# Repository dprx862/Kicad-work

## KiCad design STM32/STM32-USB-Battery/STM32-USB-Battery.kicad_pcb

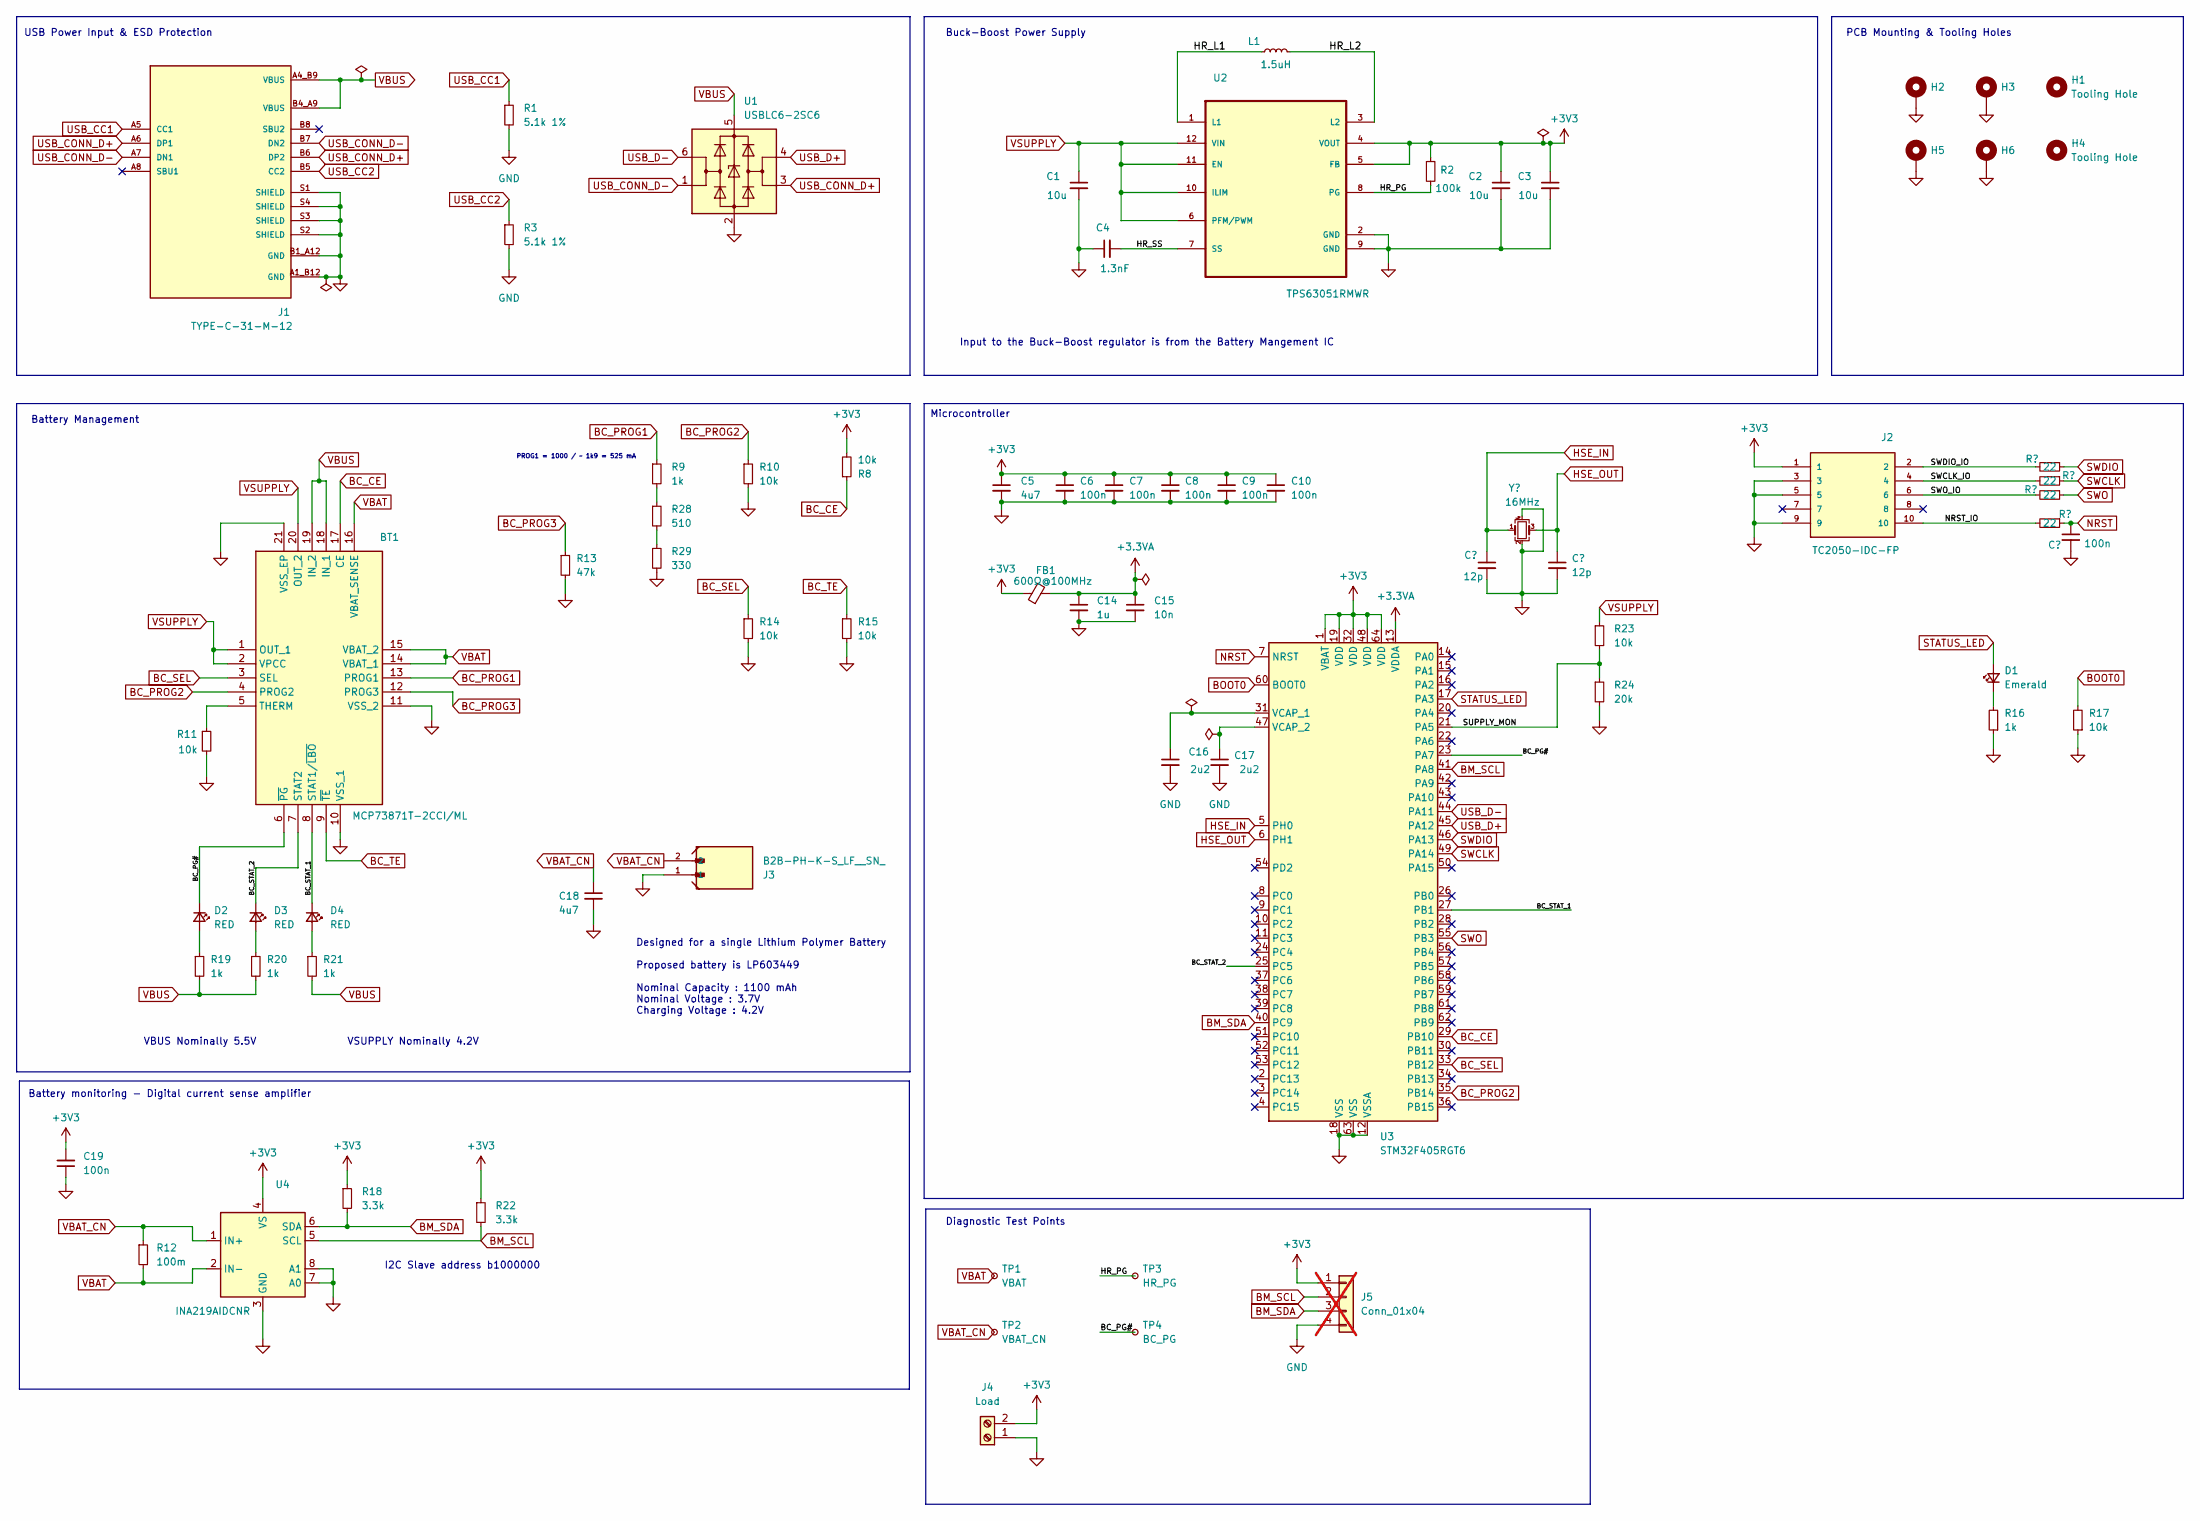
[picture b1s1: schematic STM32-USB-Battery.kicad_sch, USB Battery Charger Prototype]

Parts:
BT1: MCP73871T-2CCI/ML; QFN50P400X400X100-21M-D; Mouser Part Number 579-MCP73871T2CCIML
C1, C2, C3: 10u; C_0603_1608Metric; LCSC Part # C96446
C4: 1.3nF; C_0402_1005Metric; LCSC Part # C1523
C5, C18: 4u7; C_0603_1608Metric; LCSC Part # C19666
C6, C7, C8, C9, C10, C11, C19: 100n; C_0402_1005Metric; LCSC Part # C1525
C12, C13: 12p; C_0402_1005Metric; LCSC Part # C1547
C14: 1u; C_0402_1005Metric; LCSC Part # C52923
C15: 10n; C_0402_1005Metric; LCSC Part # C15195
C16, C17: 2u2; C_0603_1608Metric; LCSC Part # C23630
D1: Emerald; LED_0805_2012Metric; LCSC Part # C2297
D2, D3, D4: RED; LED_0603_1608Metric; LCSC Part # C2286
FB1: 600Ω@100MHz; L_0805_2012Metric; LCSC Part # C1017
H1, H4: Tooling Hole; JLC Tooling Hole
H2, H3, H5, H6: MountingHole_Pad; MountingHole_3.2mm_M3_DIN965_Pad_TopBottom
J1: TYPE-C-31-M-12; HRO_TYPE-C-31-M-12; PARTREV 2020.12.08; LCSC Part # C165948
J2: TC2050-IDC-FP; Tag-Connect_TC2050-IDC-FP_2x05_P1.27mm_Vertical
J3: B2B-PH-K-S_LF__SN_; JST_B2B-PH-K-S_LF__SN_
J4: Load; 1760510000
J5: Conn_01x04; PinHeader_1x04_P2.54mm_Vertical; not fitted
L1: 1.5uH; L_1008_2520Metric; LCSC Part # C98034
R1, R3: 5.1k 1%; R_0402_1005Metric; LCSC Part # C25905
R2: 100k; R_0402_1005Metric; LCSC Part # C25741
R4, R5, R6, R7: 22; R_0402_1005Metric; LCSC Part # C25092
R8, R10, R11, R14, R15, R17, R23: 10k; R_0402_1005Metric; LCSC Part # C25744
R9, R16, R19, R20, R21: 1k; R_0402_1005Metric; LCSC Part # C11702
R12: 100m; R_1206_3216Metric; LCSC Part # C2903496
R13: 47k; R_0402_1005Metric; LCSC Part # C25792
R18, R22: 3.3k; R_0402_1005Metric; LCSC Part # C25890
R24: 20k; R_0402_1005Metric; LCSC Part # C25765
R28: 510; R_0402_1005Metric; LCSC Part # C25123
R29: 330; R_0402_1005Metric; LCSC Part # C25104
TP1: VBAT; TestPoint_Pad_D1.0mm
TP2: VBAT_CN; TestPoint_Pad_D1.0mm
TP3: HR_PG; TestPoint_Pad_D1.0mm
TP4: BC_PG; TestPoint_Pad_D1.0mm
U1: USBLC6-2SC6; SOT-23-6; LCSC Part # C7519
U2: TPS63051RMWR; QFN50P250X250X100-12N; LCSC Part # C139412
U3: STM32F405RGT6; LQFP-64_10x10mm_P0.5mm; LCSC Part # C15742
U4: INA219AIDCNR; SOT-23-8; LCSC Part # C87469
Y1: 16MHz; Crystal_SMD_3225-4Pin_3.2x2.5mm; LCSC Part # C13738

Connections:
+3.3VA: C14.1, C15.1, FB1.2, U3.13 (VDDA)
+3V3: C2.1, C3.1, C5.1, C6.1, C7.1, C8.1, C9.1, C10.1, C19.2, FB1.1, J2.1, J4.2, J5.1, R2.1, R8.2, R18.1, R22.1, U2.4 (VOUT), U2.5 (FB), U3.1 (VBAT), U3.19 (VDD), U3.32 (VDD), U3.48 (VDD), U3.64 (VDD), U4.4 (VS)
/BC_PG#: BT1.6 (~PG), D2.1 (K), TP4.1, U3.23 (PA7)
/BC_STAT_1: BT1.8 (STAT1/~LBO), D4.1 (K), U3.27 (PB1)
/BC_STAT_2: BT1.7 (STAT2), D3.1 (K), U3.25 (PC5)
/HR_L1: L1.1, U2.1 (L1)
/HR_L2: L1.2, U2.3 (L2)
/HR_PG: R2.2, TP3.1, U2.8 (PG)
/HR_SS: C4.2, U2.7 (SS)
/NRST_IO: J2.10, R7.2
/SUPPLY_MON: R23.2, R24.1, U3.21 (PA5)
/SWCLK_IO: J2.4, R5.2
/SWDIO_IO: J2.2, R4.2
/SWO_IO: J2.6, R6.2
BC_CE: BT1.17 (CE), R8.1, U3.29 (PB10)
BC_PROG1: BT1.13 (PROG1), R9.1
BC_PROG2: BT1.4 (PROG2), R10.1, U3.35 (PB14)
BC_PROG3: BT1.12 (PROG3), R13.1
BC_SEL: BT1.3 (SEL), R14.1, U3.33 (PB12)
BC_TE: BT1.9 (~TE), R15.1
BM_SCL: J5.2, R22.2, U3.41 (PA8), U4.5 (SCL)
BM_SDA: J5.3, R18.2, U3.40 (PC9), U4.6 (SDA)
BOOT0: R17.2, U3.60 (BOOT0)
GND: BT1.10 (VSS_1), BT1.11 (VSS_2), BT1.21 (VSS_EP), C1.2, C2.2, C3.2, C4.1, C5.2, C6.2, C7.2, C8.2, C9.2, C10.2, C11.2, C12.2, C13.2, C14.2, C15.2, C16.2, C17.2, C18.2, C19.1, H2.1, H3.1, H5.1, H6.1, J1.A1_B12 (GND), J1.B1_A12 (GND), J1.S1 (SHIELD), J1.S2 (SHIELD), J1.S3 (SHIELD), J1.S4 (SHIELD), J2.3, J2.5, J2.9, J3.1, J4.1, J5.4, R1.2, R3.2, R10.2, R11.2, R13.2, R14.2, R15.2, R16.1, R17.1, R24.2, R29.2, U1.2 (GND), U2.2 (GND), U2.9 (GND), U3.12 (VSSA), U3.18 (VSS), U3.63 (VSS), U4.3 (GND), U4.7 (A0), U4.8 (A1), Y1.2, Y1.4
HSE_IN: C12.1, U3.5 (PH0), Y1.1
HSE_OUT: C13.1, U3.6 (PH1), Y1.3
NRST: C11.1, R7.1, U3.7 (NRST)
unnamed: BT1.5 (THERM), R11.1
unnamed: D1.1 (K), R16.2
unnamed: D2.2 (A), R19.1
unnamed: D3.2 (A), R20.1
unnamed: D4.2 (A), R21.1
unnamed: R9.2, R28.1
unnamed: R28.2, R29.1
unnamed: C16.1, U3.31 (VCAP_1)
unnamed: C17.1, U3.47 (VCAP_2)
STATUS_LED: D1.2 (A), U3.17 (PA3)
SWCLK: R5.1, U3.49 (PA14)
SWDIO: R4.1, U3.46 (PA13)
SWO: R6.1, U3.55 (PB3)
USB_CC1: J1.A5 (CC1), R1.1
USB_CC2: J1.B5 (CC2), R3.1
USB_CONN_D+: J1.A6 (DP1), J1.B6 (DP2), U1.3 (I/O2)
USB_CONN_D-: J1.A7 (DN1), J1.B7 (DN2), U1.1 (I/O1)
USB_D+: U1.4 (I/O2), U3.45 (PA12)
USB_D-: U1.6 (I/O1), U3.44 (PA11)
VBAT: BT1.14 (VBAT_1), BT1.15 (VBAT_2), BT1.16 (VBAT_SENSE), R12.2, TP1.1, U4.2 (IN-)
VBAT_CN: C18.1, J3.2, R12.1, TP2.1, U4.1 (IN+)
VBUS: BT1.18 (IN_1), BT1.19 (IN_2), J1.A4_B9 (VBUS), J1.B4_A9 (VBUS), R19.2, R20.2, R21.2, U1.5 (VBUS)
VSUPPLY: BT1.1 (OUT_1), BT1.2 (VPCC), BT1.20 (OUT_2), C1.1, R23.1, U2.6 (PFM/PWM), U2.10 (ILIM), U2.11 (EN), U2.12 (VIN)

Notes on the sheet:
Microcontroller
USB Power Input & ESD Protection
Battery Management
Input to the Buck-Boost regulator is from the Battery Mangement IC
Diagnostic Test Points
Buck-Boost Power Supply
PCB Mounting & Tooling Holes
VBUS Nominally 5.5V VSUPPLY Nominally 4.2V
PROG1 = 1000 / ~ 1k9 = 525 mA
Battery monitoring - Digital current sense amplifier
I2C Slave address b1000000
Designed for a single Lithium Polymer Battery Proposed battery is LP603449 Nominal Capacity : 1100 mAh Nominal Voltage : 3.7V Charging Voltage : 4.2V

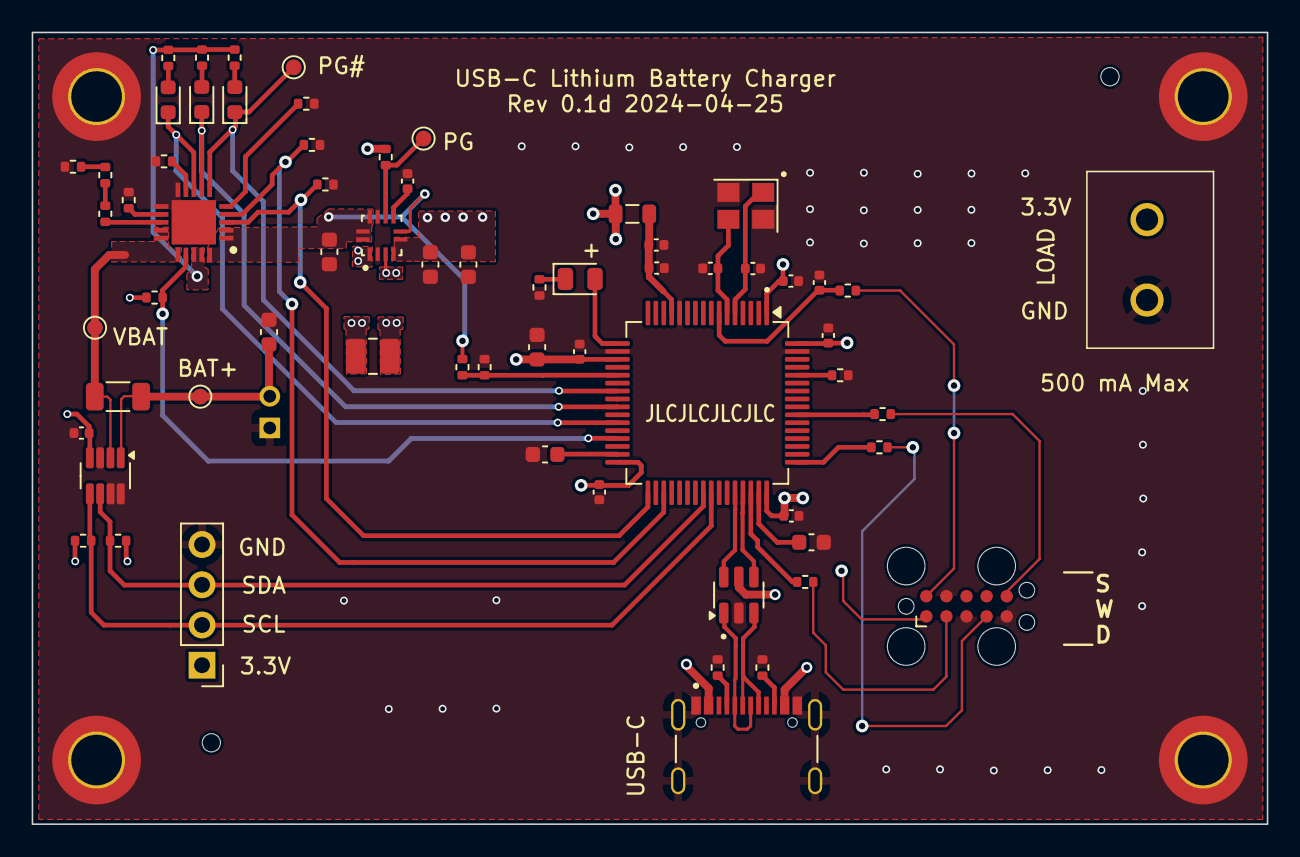
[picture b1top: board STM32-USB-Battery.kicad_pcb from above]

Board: 4 copper layers, 78.0 x 50.0 mm, 72 parts (1 on the bottom side), 50 nets.

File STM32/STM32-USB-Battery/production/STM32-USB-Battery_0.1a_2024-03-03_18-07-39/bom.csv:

Designator,Footprint,Quantity,Value,LCSC Part #
BT1,QFN50P400X400X100-21M-D,1,MCP73871T-2CCI/ML,C511310
"C1, C2, C3",0603,3,10u,C96446
"C10, C11, C19, C6, C7, C8, C9",0402,7,100n,C1525
"C12, C13",0402,2,12p,C1547
C14,0402,1,1u,C52923
C15,0402,1,10n,C15195
"C16, C17",0603,2,2u2,C23630
"C18, C5",0603,2,4u7,C19666
C4,0402,1,1.3nF,C1523
D1,0805,1,Emerald,C2297
"D2, D3, D4",0603,3,RED,C2286
FB1,0805,1,600Ω@100MHz,C1017
J1,HRO_TYPE-C-31-M-12,1,TYPE-C-31-M-12,C165948
J3,JST_B2B-PH-K-S_LF__SN_,1,B2B-PH-K-S_LF__SN_,
L1,1008,1,1.5uH,C98034
"R1, R3",0402,2,5.1k 1%,C25905
"R10, R11, R14, R15, R17, R23, R8",0402,7,10k,C25744
R12,1206,1,100m,C2903496
"R13, R2",0402,2,100k,C25741
"R16, R19, R20, R21",0402,4,1k,C11702
"R18, R22",0402,2,3.3k,C25890
R24,0402,1,20k,C25765
R28,0402,1,4k7,C25900
"R4, R5, R6, R7",0402,4,22,C25092
R9,0402,1,3k3,C25890
TP1,TestPoint_Pad_D1.0mm,1,VBAT,
TP2,TestPoint_Pad_D1.0mm,1,VBAT_CN,
TP3,TestPoint_Pad_D1.0mm,1,HR_PG,
TP4,TestPoint_Pad_D1.0mm,1,BC_PG,
U1,SOT-23-6,1,USBLC6-2SC6,C7519
U2,QFN50P250X250X100-12N,1,TPS63051RMWR,C139412
U3,LQFP-64_10x10mm_P0.5mm,1,STM32F405RGT6,C15742
U4,SOT-23-8,1,INA219AxDCN,C87469
Y1,Crystal_SMD_3225-4Pin_3.2x2.5mm,1,16MHz,C13738

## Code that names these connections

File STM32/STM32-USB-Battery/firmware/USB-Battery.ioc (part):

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Mcu.Name=STM32F405RGTx
Mcu.Package=LQFP64
Mcu.UserName=STM32F405RGTx
PA11.GPIOParameters=GPIO_Label
PA11.GPIO_Label=USB_D-
PA11.Mode=Device_Only
PA11.Signal=USB_OTG_FS_DM
PA12.GPIOParameters=GPIO_Label
PA12.GPIO_Label=USB_D+
PA12.Mode=Device_Only
PA12.Signal=USB_OTG_FS_DP
PA13.Mode=Trace_Asynchronous_SW
PA13.Signal=SYS_JTMS-SWDIO
PA14.Mode=Trace_Asynchronous_SW
PA14.Signal=SYS_JTCK-SWCLK
PA3.GPIOParameters=GPIO_Label
PA3.GPIO_Label=STATUS_LED
PA3.Signal=GPIO_Output
PA5.GPIOParameters=GPIO_Label
PA5.GPIO_Label=SUPPLY_MON
PA5.Signal=ADCx_IN5
PA7.GPIOParameters=GPIO_PuPd,GPIO_Label
PA7.GPIO_Label=BC_STAT_PG
PA7.GPIO_PuPd=GPIO_NOPULL
PA7.Signal=GPIO_Input
PA8.Mode=I2C
PA8.Signal=I2C3_SCL
PB1.GPIOParameters=GPIO_PuPd,GPIO_Label
PB1.GPIO_Label=BC_STAT_1
PB1.GPIO_PuPd=GPIO_NOPULL
PB1.Signal=GPIO_Input
PB10.GPIOParameters=GPIO_Label
PB10.GPIO_Label=BC_CE
PB10.Signal=GPIO_Output
PB12.GPIOParameters=GPIO_Label
PB12.GPIO_Label=BC_SEL
PB12.Signal=GPIO_Output
PB14.GPIOParameters=PinState,GPIO_Label
PB14.GPIO_Label=BC_PROG2
PB14.PinState=GPIO_PIN_SET
PB14.Signal=GPIO_Output
PB3.Mode=Trace_Asynchronous_SW
PB3.Signal=SYS_JTDO-SWO
PC5.GPIOParameters=GPIO_Label
PC5.GPIO_Label=BC_STAT_2
PC5.Signal=GPIO_Input
PC9.Mode=I2C
PC9.Signal=I2C3_SDA
PH0-OSC_IN.GPIOParameters=GPIO_Label
PH0-OSC_IN.GPIO_Label=HSE_IN
PH0-OSC_IN.Mode=HSE-External-Oscillator
PH0-OSC_IN.Signal=RCC_OSC_IN
PH1-OSC_OUT.GPIOParameters=GPIO_Label
PH1-OSC_OUT.GPIO_Label=HSE_OUT
PH1-OSC_OUT.Mode=HSE-External-Oscillator
PH1-OSC_OUT.Signal=RCC_OSC_OUT
RCC.HSE_VALUE=16000000
RCC.SYSCLKFreq_VALUE=168000000
RCC.SYSCLKSource=RCC_SYSCLKSOURCE_PLLCLK
board=custom

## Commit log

2024-11-23 Commit for external repo
2024-11-23 Remove hard coded paths
